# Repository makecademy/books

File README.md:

Ressources for the Open Home Automation books
=====

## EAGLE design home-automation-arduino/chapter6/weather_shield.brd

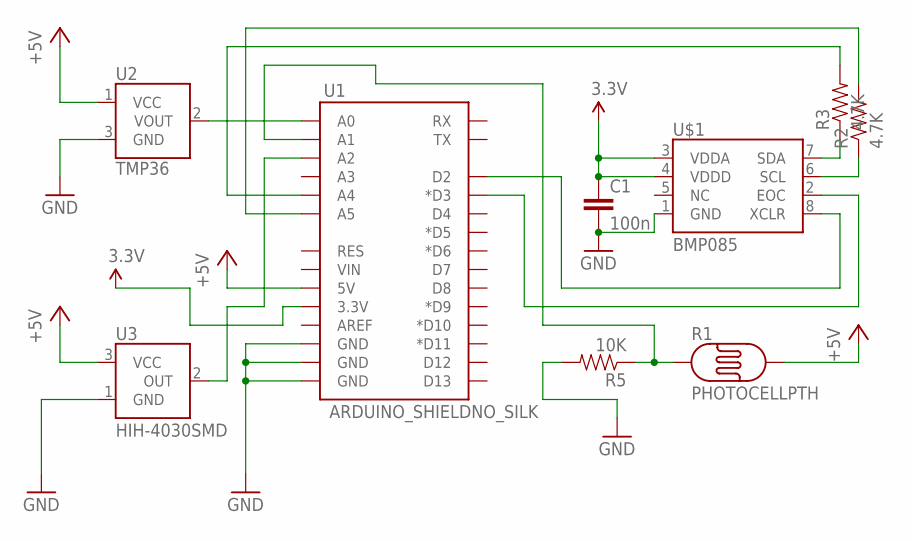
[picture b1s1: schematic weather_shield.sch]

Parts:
C1: 100n; 1206
R1: PHOTOCELLPTH; PHOTOCELL
R2, R3: 4.7K; 1206
R5: 10K; 1206
U1: ARDUINO_SHIELDNO_SILK; DUEMILANOVE_VIAS
U2: TMP36; TO-92
U3: HIH-4030SMD; HIH-4030
U$1: BMP085

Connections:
3.3V: C1.1, U1.3.3V, U$1.3 (VDDA), U$1.4 (VDDD)
+5V: R1.2, U1.5V, U2.1 (VCC), U3.3 (VCC)
GND: C1.2, R5.2, U1.GND@0 (GND), U1.GND@1 (GND), U1.GND@2 (GND), U2.3 (GND), U3.1 (GND), U$1.1 (GND)
unnamed: R1.1, R5.1, U1.A1
unnamed: U1.A2, U3.2 (OUT)
unnamed: U1.A0, U2.2 (VOUT)
unnamed: R3.1, U$1.7 (SDA)
unnamed: R2.1, U$1.6 (SCL)
unnamed: U1.D2, U$1.8 (XCLR)
unnamed: R3.2, U1.A4
unnamed: R2.2, U1.A5
unnamed: U1.D3 (*D3), U$1.2 (EOC)

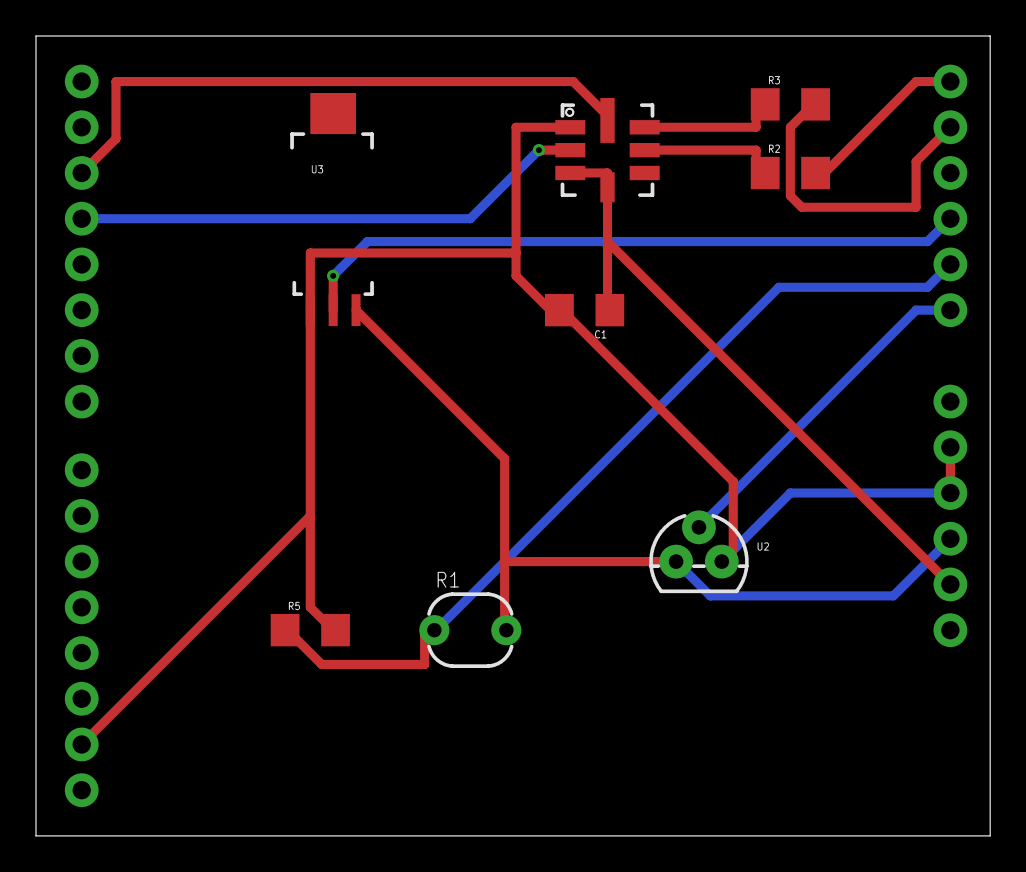
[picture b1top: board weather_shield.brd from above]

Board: 2 copper layers, 53.0 x 44.4 mm, 9 parts (0 on the bottom side), 12 nets.

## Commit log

2013-06-19 repo organization and first files
2013-06-19 chapter 2 complete
2013-06-19 chapter 3 done
2013-06-19 chapter 4 done
2013-06-19 all done
2013-06-20 finished chapter5
2013-09-14 chapter 3 fixed
2013-09-14 plot using flot fixed
2013-09-15 fix in temperature readout
2013-09-17 fixes in chapter 1
2013-09-17 fixes in Arduino sketches
2014-02-26 small fixes
2014-02-26 added changes for chapter 3
2014-02-26 added changes for chapter 3 and fixes
2014-02-26 first add chapter 6
2014-02-26 chapter 6 fixes

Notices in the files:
parts and their libraries:
SparkFun-Boards: Licensing: CC v3.0 Share-Alike You are welcome to use this library for commercial purposes.
